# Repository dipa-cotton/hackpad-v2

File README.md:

# hackpad-v2
hi! This is my second version of my macropad (you can find the first @dizzles-hackpad). It has 7 buttons, 2 rotary encoders, an OLED, a xiao rp2040 as the microcontroller, and more! I'm pretty proud of my project as this is only my 3rd time using KiCAD, and I think i did pretty well. My goal in building this was to use up the extra parts I recieved with my first hackpad kit. yay!
PCB Routed

Schematic

3D Render

BOM and Shopping Carts

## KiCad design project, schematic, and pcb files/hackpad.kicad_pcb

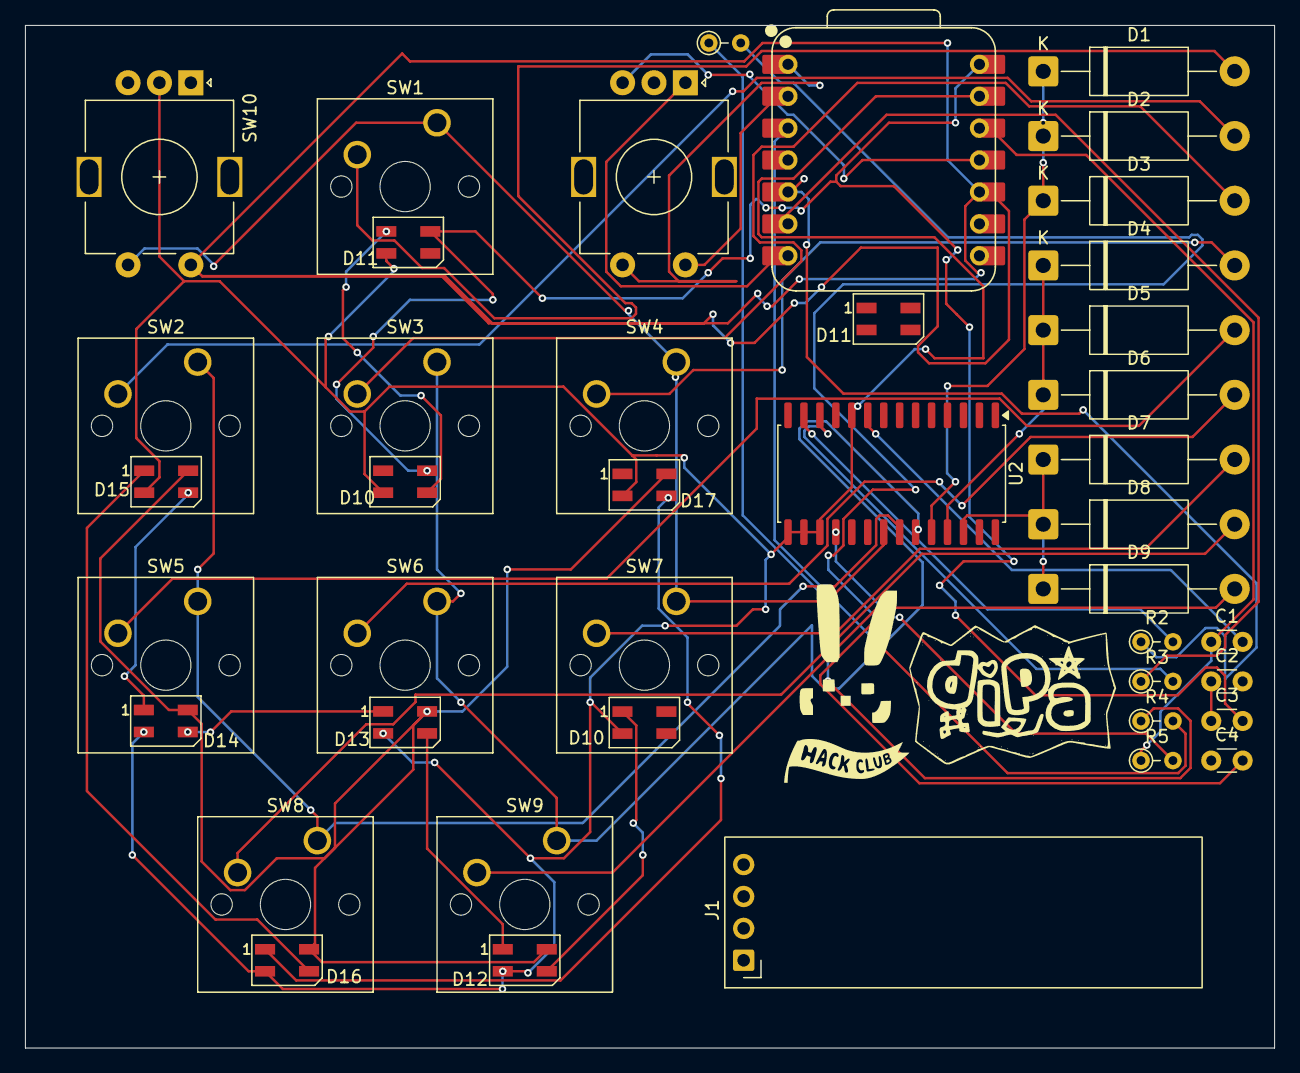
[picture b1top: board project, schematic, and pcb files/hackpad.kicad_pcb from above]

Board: 2 copper layers, 99.4 x 81.4 mm, 42 parts (0 on the bottom side), 41 nets.

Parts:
C1, C2, C3, C4: 100nF; C_Disc_D3.0mm_W1.6mm_P2.50mm
D1, D2, D3, D4, D5, D6, D7, D8, D9: D; D_DO-15_P15.24mm_Horizontal
D10, D10#2, D11, D11#2, D12, D13, D14, D15, D16, D17: SK6812MINI; LED_SK6812MINI_PLCC4_3.5x3.5mm_P1.75mm
J1: Conn_01x04_Pin; OLED_0.91_128x32
R1: 330 ohm; R_Axial_DIN0204_L3.6mm_D1.6mm_P2.54mm_Vertical
R2, R3: 4.7k; R_Axial_DIN0204_L3.6mm_D1.6mm_P2.54mm_Vertical
R4: 330ohm; R_Axial_DIN0204_L3.6mm_D1.6mm_P2.54mm_Vertical
R5: 10k; R_Axial_DIN0204_L3.6mm_D1.6mm_P2.54mm_Vertical
SW1, SW2, SW3, SW4, SW5, SW6, SW7, SW8, SW9: SW_Push; SW_Cherry_MX_1.00u_PCB
SW10, SW11: RotaryEncoder_Switch; RotaryEncoder_Alps_EC11E-Switch_Vertical_H20mm
U1: XIAO-RP2040-DIP
U2: MCP23017_SO; SOIC-28W_7.5x17.9mm_P1.27mm

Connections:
3V3: C1.1, R5.1, U1.12 (3V3)
+5V: C3.2, D10#2.4 (VDD), D11.4 (VDD), U1.14 (VBUS)
A: SW11.A, U1.7 (GPIO0/TX)
B: SW11.B, U1.11 (GPIO3/MOSI)
COL1: D1.1 (K), D2.1 (K), D3.1 (K), U2.24 (GPA3)
COL2: D4.1 (K), D5.1 (K), D6.1 (K), U2.25 (GPA4)
COL3: D7.1 (K), D8.1 (K), D9.1 (K), U2.26 (GPA5)
Col2: SW10.S2, U1.10 (GPIO4/MISO)
EC11SWA: SW1.1, SW4.1, SW7.1, SW10.S1, U2.21 (GPA0)
GND: D10.2 (VSS), D10#2.2 (VSS), D11.2 (VSS), D12.2 (VSS), D13.2 (VSS), D14.2 (VSS), D15.2 (VSS), D16.2 (VSS), D17.2 (VSS), SW10.C, U1.13 (GND), U2.10 (VSS), U2.15 (A0), U2.16 (A1), U2.17 (A2)
unnamed: C2.1, C3.1
unnamed: C4.2, R1.2
unnamed: D1.2 (A), SW1.2
unnamed: D10#2.3 (DIN), D11.1 (DOUT)
unnamed: D2.2 (A), SW2.2
unnamed: D3.2 (A), SW3.2
unnamed: D4.2 (A), SW4.2
unnamed: D5.2 (A), SW5.2
unnamed: D6.2 (A), SW6.2
unnamed: D7.2 (A), SW7.2
unnamed: D8.2 (A), SW8.2
unnamed: D9.2 (A), SW9.2
unnamed: D10.1 (DOUT), D12.3 (DIN)
unnamed: D12.4 (VDD), D13.4 (VDD), D14.4 (VDD), D15.4 (VDD), D16.4 (VDD), D17.4 (VDD)
unnamed: D12.1 (DOUT), D13.3 (DIN)
unnamed: D13.1 (DOUT), D14.3 (DIN)
unnamed: D14.1 (DOUT), D15.3 (DIN)
unnamed: D15.1 (DOUT), D16.3 (DIN)
unnamed: D16.1 (DOUT), D17.3 (DIN)
unnamed: R2.1, U1.5 (GPIO6/SDA)
unnamed: R3.1, U1.6 (GPIO7/SCL)
unnamed: R4.2, U1.3 (GPIO28/ADC2/A2)
unnamed: C1.2, U2.9 (VDD)
unnamed: R5.2, U2.18 (~RESET)
ROW1: SW2.1, SW5.1, SW8.1, U2.22 (GPA1)
ROW2: SW3.1, SW6.1, SW9.1, U2.23 (GPA2)
S1: SW11.S1, U1.1 (GPIO26/ADC0/A0)
S2: SW11.S2, U1.2 (GPIO27/ADC1/A1)
SCK: R3.2, U2.12 (SCK)
SDA: R2.2, U2.13 (SDA)
WS2812B: R1.1, R4.1

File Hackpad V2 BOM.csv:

Reference,Qty,Object,Footprint,Price,Link
"C1,C2,C3,C4",4,100nF,Capacitor_THT:C_Disc_D3.0mm_W1.6mm_P2.50mm,1.04,https://www.digikey.com/en/products/detail/kemet/C0603C102F8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
"D1,D2",2,SK6812MINI,LED_SMD:LED_SK6812MINI_PLCC4_3.5x3.5mm_P1.75mm,Owned,
J1,1,Conn_01x04_Pin,Connector:FanPinHeader_1x04_P2.54mm_Vertical,Owned,
R1,1,330 ohm,Resistor_THT:R_Axial_DIN0204_L3.6mm_D1.6mm_P2.54mm_Vertical,1.29,https://www.aliexpress.us/item/2251832766343175.html?spm=a2g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
"R2,R3,R4,R5",4,4.7k,Resistor_THT:R_Axial_DIN0204_L3.6mm_D1.6mm_P2.54mm_Vertical,5,https://www.aliexpress.us/item/3256810275816470.html?spm=a2g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
"SW1,SW2,SW3,SW4,SW5,SW6,SW7,SW8,SW9",9,SW_Push,Button_Switch_Keyboard:SW_Cherry_MX_1.00u_PCB,Owned,
"SW10,SW11",2,RotaryEncoder_Switch,Rotary_Encoder:RotaryEncoder_Alps_EC11E-Switch_Vertical_H20mm,Owned,
U1,1,XIAO-RP2040-DIP,Module:MOUDLE14P-XIAO-DIP-SMD,3.9,https://www.seeedstudio.com/XIAO-RP2040-v1-0-p-5026.html
U2,1,PCF8574AP,Package_DIP:DIP-16_W7.62mm,3.38,https://www.aliexpress.us/item/3256806116951581.html?spm=a2g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
,,,,14.61,
,,,,+ 8 for pcb,
,,,,+10 for shipping,
,,,Total:,$33 ,

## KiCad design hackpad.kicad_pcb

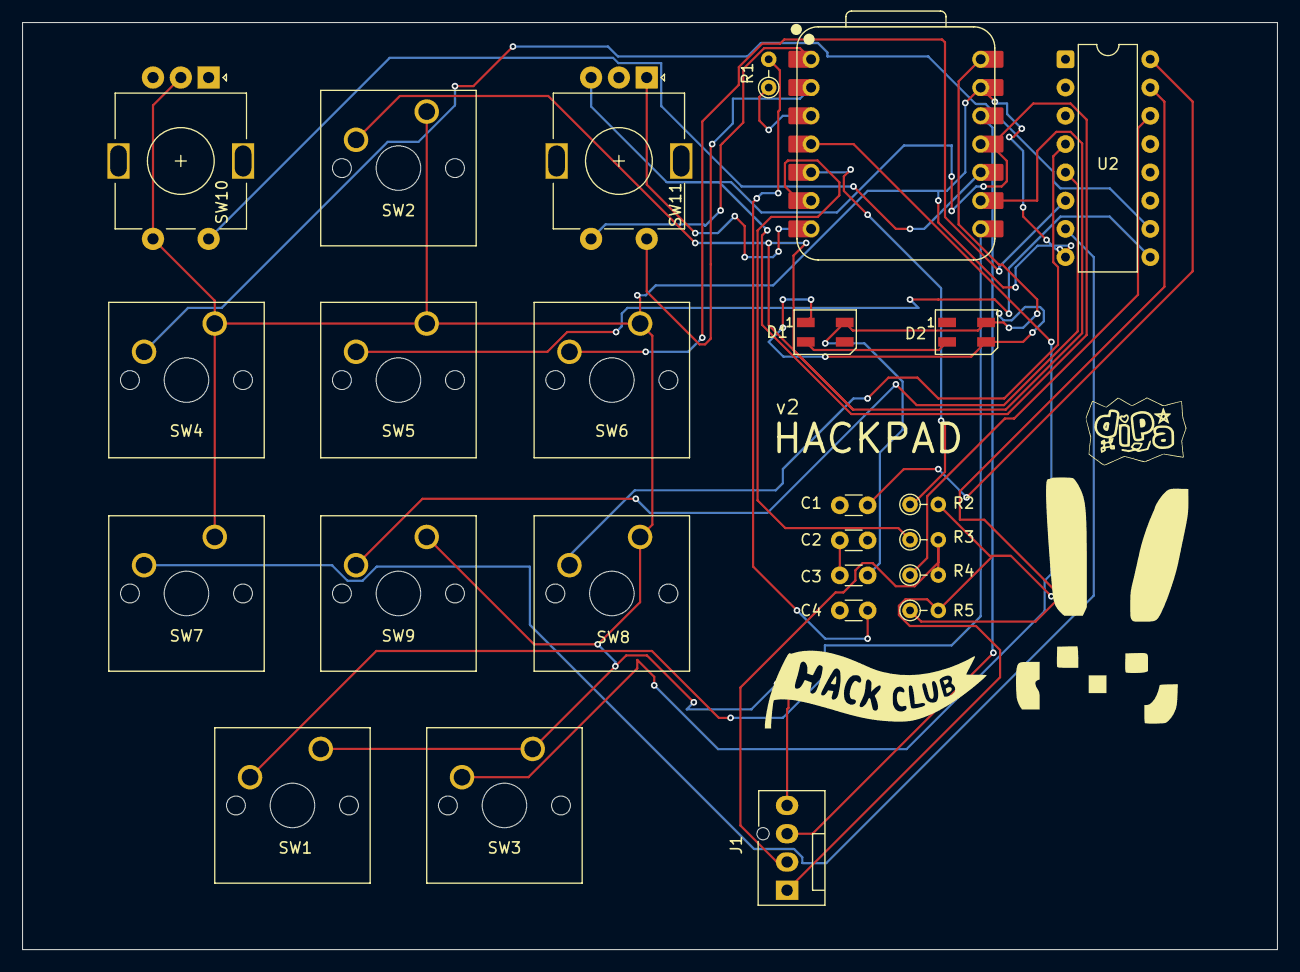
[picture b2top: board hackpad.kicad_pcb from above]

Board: 2 copper layers, 112.8 x 83.3 mm, 25 parts (0 on the bottom side), 29 nets.

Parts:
C1, C2, C3, C4: 100nF; C_Disc_D3.0mm_W1.6mm_P2.50mm
D1, D2: SK6812MINI; LED_SK6812MINI_PLCC4_3.5x3.5mm_P1.75mm
J1: Conn_01x04_Pin; FanPinHeader_1x04_P2.54mm_Vertical
R1: 330 ohm; R_Axial_DIN0204_L3.6mm_D1.6mm_P2.54mm_Vertical
R2, R3, R4, R5: 4.7k; R_Axial_DIN0204_L3.6mm_D1.6mm_P2.54mm_Vertical
SW1, SW2, SW3, SW4, SW5, SW6, SW7, SW8, SW9: SW_Push; SW_Cherry_MX_1.00u_PCB
SW10, SW11: RotaryEncoder_Switch; RotaryEncoder_Alps_EC11E-Switch_Vertical_H20mm
U1: XIAO-RP2040-DIP
U2: PCF8574AP; DIP-16_W7.62mm

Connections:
3V3: J1.3, U1.12 (3V3)
+5V: C3.2, D1.4 (VDD), D2.4 (VDD), U1.14 (VBUS)
A: SW11.A, U1.7 (GPIO0/TX)
B: SW11.B, U1.11 (GPIO3/MOSI)
Col2: SW10.S2, U1.10 (GPIO4/MISO)
EC11SWA: J1.4, SW1.1, SW2.1, SW3.1, SW4.1, SW5.1, SW6.1, SW7.1, SW8.1, SW9.1, SW10.C, SW10.S1, U1.13 (GND), U2.8 (GND)
GND: D1.2 (VSS), D2.2 (VSS)
unnamed: C2.1, C3.1
unnamed: C4.2, R1.2
unnamed: D1.1 (DOUT), D2.3 (DIN)
unnamed: R2.1, U1.5 (GPIO6/SDA)
unnamed: R3.1, U1.6 (GPIO7/SCL)
unnamed: R4.1, U2.14 (SCL)
unnamed: R5.1, U2.15 (SDA)
unnamed: C1.2, U2.16 (VDD)
S1: SW11.S1, U1.1 (GPIO26/ADC0/A0)
S2: SW11.S2, U1.2 (GPIO27/ADC1/A1)
SCK: J1.2, R3.2, R4.2
SDA: J1.1, R2.2, R5.2
SWitch 1: SW1.2, U1.8 (GPIO1/RX)
SWitch 2: SW2.2, U1.9 (GPIO2/SCK)
SWitch 3: SW3.2, U1.4 (GPIO29/ADC3/A3)
SWitch 4: SW4.2, U2.10 (P5)
SWitch 5: SW5.2, U2.9 (P4)
SWitch 6: SW6.2, U2.6 (P2)
SWitch 7: SW7.2, U2.7 (P3)
SWitch 8: SW8.2, U2.4 (P0)
SWitch 9: SW9.2, U2.5 (P1)
WS2812B: R1.1, U1.3 (GPIO28/ADC2/A2)

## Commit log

2026-02-03 Create h
2026-02-04 Update README with images and PCB details
    Added images and PCB routing information to the README.
2026-02-04 Update README.md with new images and sections
2026-04-12 Update README with new images and descriptions
    Added additional images for PCB, schematic, and 3D render sections.
2026-04-12 Create project, pcb, and schematic files
2026-04-12 Add additional images to README.md
